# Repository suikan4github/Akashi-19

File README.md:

# Akashi-19
Raspberry Pi Pico Breadboard platform. 

# Details

A board with Raspberry Pi and Breadboard together. 

Features :
- Support two popular bread boards. 
- Pin labels next to the sockets. 
- Reset switch. 
- UART connector ( FTDI pin assign ).
- QWIIC connector ( 3.5V Vdd / 3.3V signal ).
- GROVE connector ( 5.0V Vdd / 3.3V signal )

The circuit schematics are available [here](docs/Akashi-19.pdf).

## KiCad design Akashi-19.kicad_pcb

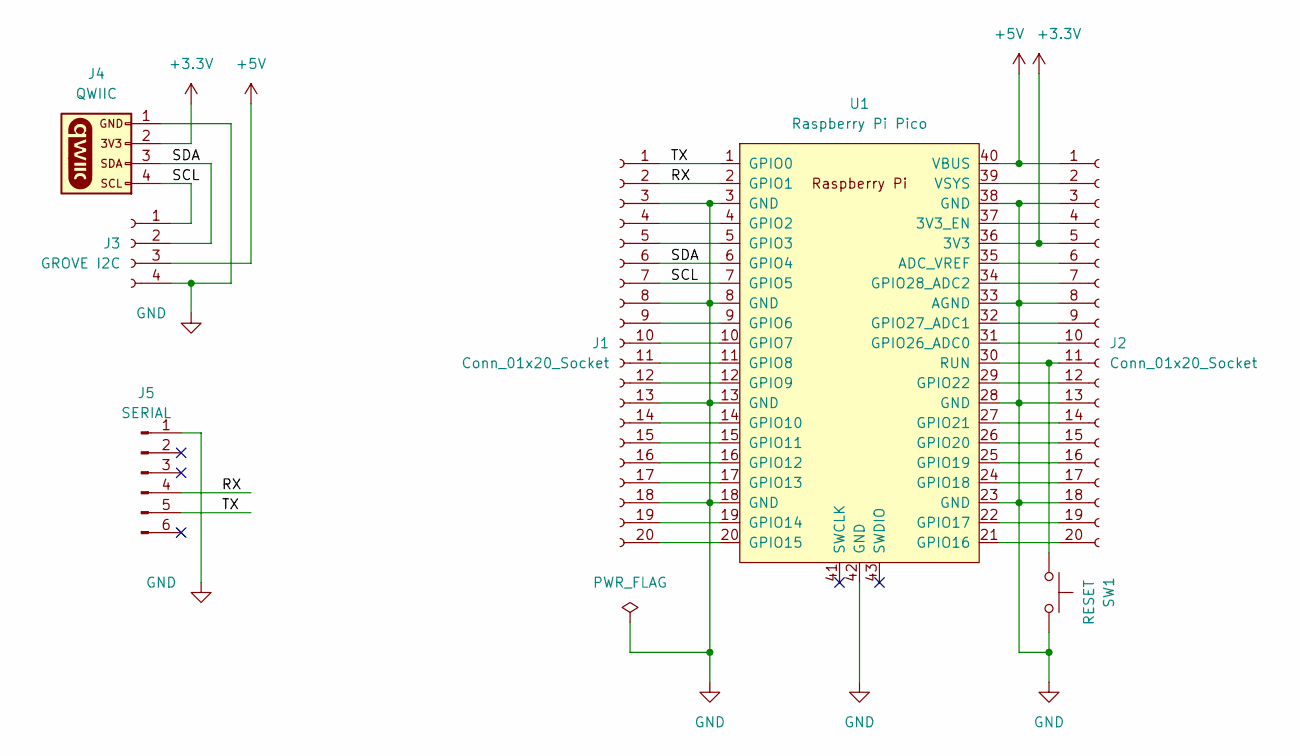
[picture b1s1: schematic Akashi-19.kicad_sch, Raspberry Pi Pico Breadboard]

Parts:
J1, J2: Conn_01x20_Socket; PinSocket_1x20_P2.54mm_Vertical
J3: GROVE I2C; NS-Tech_Grove_1x04_P2mm_Vertical
J4: QWIIC; JST04_1MM_RA
J5: SERIAL; PinHeader_1x06_P2.54mm_Horizontal
SW1: RESET; SW_TH_Tactile_Omron_B3F-10xx
U1: Raspberry Pi Pico; RPi_Pico_SMD_TH

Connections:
+3.3V: J2.5, J4.2, U1.36 (3V3)
+5V: J2.1, J3.3, U1.40 (VBUS)
/RX: J1.2, J5.4, U1.2 (GPIO1)
/SCL: J1.7, J3.1, J4.4, U1.7 (GPIO5)
/SDA: J1.6, J3.2, J4.3, U1.6 (GPIO4)
/TX: J1.1, J5.5, U1.1 (GPIO0)
GND: J1.3, J1.8, J1.13, J1.18, J2.3, J2.8, J2.13, J2.18, J3.4, J4.1, J5.1, SW1.2, U1.3 (GND), U1.8 (GND), U1.13 (GND), U1.18 (GND), U1.23 (GND), U1.28 (GND), U1.33 (AGND), U1.38 (GND), U1.42 (GND)
unnamed: J1.4, U1.4 (GPIO2)
unnamed: J1.5, U1.5 (GPIO3)
unnamed: J1.9, U1.9 (GPIO6)
unnamed: J1.10, U1.10 (GPIO7)
unnamed: J1.11, U1.11 (GPIO8)
unnamed: J1.12, U1.12 (GPIO9)
unnamed: J1.14, U1.14 (GPIO10)
unnamed: J1.15, U1.15 (GPIO11)
unnamed: J1.16, U1.16 (GPIO12)
unnamed: J1.17, U1.17 (GPIO13)
unnamed: J1.19, U1.19 (GPIO14)
unnamed: J1.20, U1.20 (GPIO15)
unnamed: J2.2, U1.39 (VSYS)
unnamed: J2.4, U1.37 (3V3_EN)
unnamed: J2.6, U1.35 (ADC_VREF)
unnamed: J2.7, U1.34 (GPIO28_ADC2)
unnamed: J2.9, U1.32 (GPIO27_ADC1)
unnamed: J2.10, U1.31 (GPIO26_ADC0)
unnamed: J2.11, SW1.1, U1.30 (RUN)
unnamed: J2.12, U1.29 (GPIO22)
unnamed: J2.14, U1.27 (GPIO21)
unnamed: J2.15, U1.26 (GPIO20)
unnamed: J2.16, U1.25 (GPIO19)
unnamed: J2.17, U1.24 (GPIO18)
unnamed: J2.19, U1.22 (GPIO17)
unnamed: J2.20, U1.21 (GPIO16)

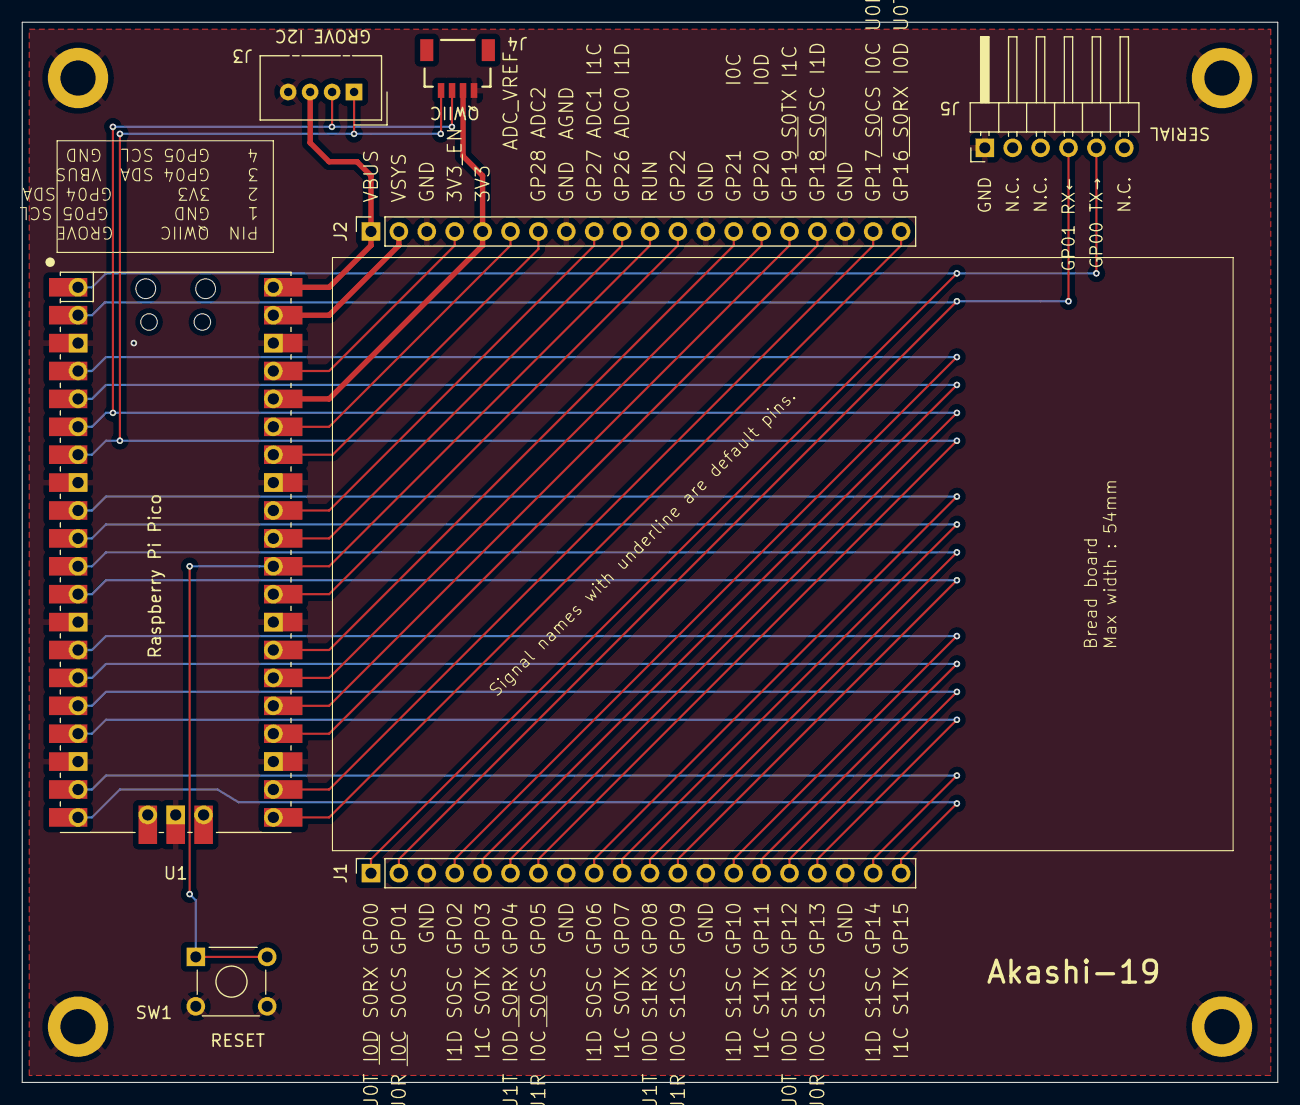
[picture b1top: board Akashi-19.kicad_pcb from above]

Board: 2 copper layers, 114.3 x 96.5 mm, 7 parts (0 on the bottom side), 33 nets.

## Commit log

2024-10-26 Add initial files.
2024-10-26 README updated.
2024-10-26 Before auto routing.
2024-10-26 DRC passed.
2024-10-26 Add Serial port and text information.
2024-10-26 Refine the text.
2024-10-26 Part position updated.
    Wire is more beautiful.
2024-10-26 Board resized.
    111.7mm length.
2024-10-27 Change pin names font to NOTO SANS MONO
2024-10-27 Pin name description is updated.
    - Separated by ' '.
    - Grove and Qwiik description by table.
2024-10-27 The font of Signal name has been changed.
    Now, Ubuntu Mono. 1.1mm
2024-10-27 Fix the text.
    VSYS -> VBUS.
2024-10-27 Schematcis was not saved correctly.
2024-10-27 Adjust the silk screen.
    - Change > to →
    - Adjust the position of through hole to show silk better.
2024-10-27 Renumbered J1, J2, J3.
2024-10-27 Add 1 pin mark to the Pico socket.
2024-10-27 Move the position of "ADC_VREF" silk.
2024-10-27 Shrunk the board size.
    To meet 100mm x 100mm
2024-10-27 Make sub-board.
2024-10-27 Added board alignment mark.
2024-10-27 Revert "Added board alignment mark."
    This reverts commit 75f44bb85ef9d02030d6fd930b5a75a72c5340a0.
2024-10-27 Revert "Make sub-board."
    This reverts commit c7701d24e49460d07e020bbc159ac3fd617b78aa.
2024-10-28 Revert "Shrunk the board size."
    This reverts commit b54ff650734e98fba3bdec88f9c05931a11ba9a0.
2024-10-28 Adjust font size and remove the signal name from debug port.
2024-10-28 Refine the size comment.
2024-10-28 Correct the wrong connection of Qwiic.
    The connection was right-side-left.
2024-10-28 Correct the wrong description of QWIIC.
2024-10-28 Add "N.C." explicitly to the pin description of serial port.
2024-10-28 Expand board size by 2.54mm.
    To give the margin to the breadboad.
2024-10-28 Adjust the postion of SW and serial port.
2024-10-28 Refine the wires for the signal integrity.
    - Connect GND pin of SWD.
    - Move some wire to give the space to GND.
2024-10-28 Adjust the position of silk screen.
2024-10-28 Holes are substituted with the official mounting holes.
2024-10-28 Ordered gerber. 2024/Oct/29 to JLCPCB.
2024-11-09 Updated README.md.
2024-11-09 Update README. Added schematics.
2024-11-09 Update README.
    Explain QWIIC signal voltage.
2024-11-09 Add changelog.
